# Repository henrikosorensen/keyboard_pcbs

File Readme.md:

GPLV2 licensed replacement keyboard PCBs.

# Omnikey 
Requires an Teensy++ 2.0 controller. - Firmware at https://github.com/qmk/qmk_firmware/tree/master/keyboards/omnikeyish

## Changelog

#### 1.3
* Nav cluster to Numpad cluster distance was off by 1/32 of an inch (0.7935mm). Meassurement confirmed on two original Omnikey PCBs and Plus rev3 plate. Not quite sure how I managed to assemble the first board.
* Rev1/3 Mounting holes got jumbled up in Schematic Reorganisation. Fixed now.

#### 1.1
* Teensy++ 2.0 uses pin D6 for an LED, so that interfers with the ROW5 assignment used on 1.0 boards. Moved ROW5 to pin E6

# AT101
Requires an Teensy 2.0 controller 

## Changelog

### 1.1
* Nav and numeric cluster distances to the alpha block were off by 1/32 inch.
* Big Arse Enter footprint updated, so stabiliser hole is large enough.

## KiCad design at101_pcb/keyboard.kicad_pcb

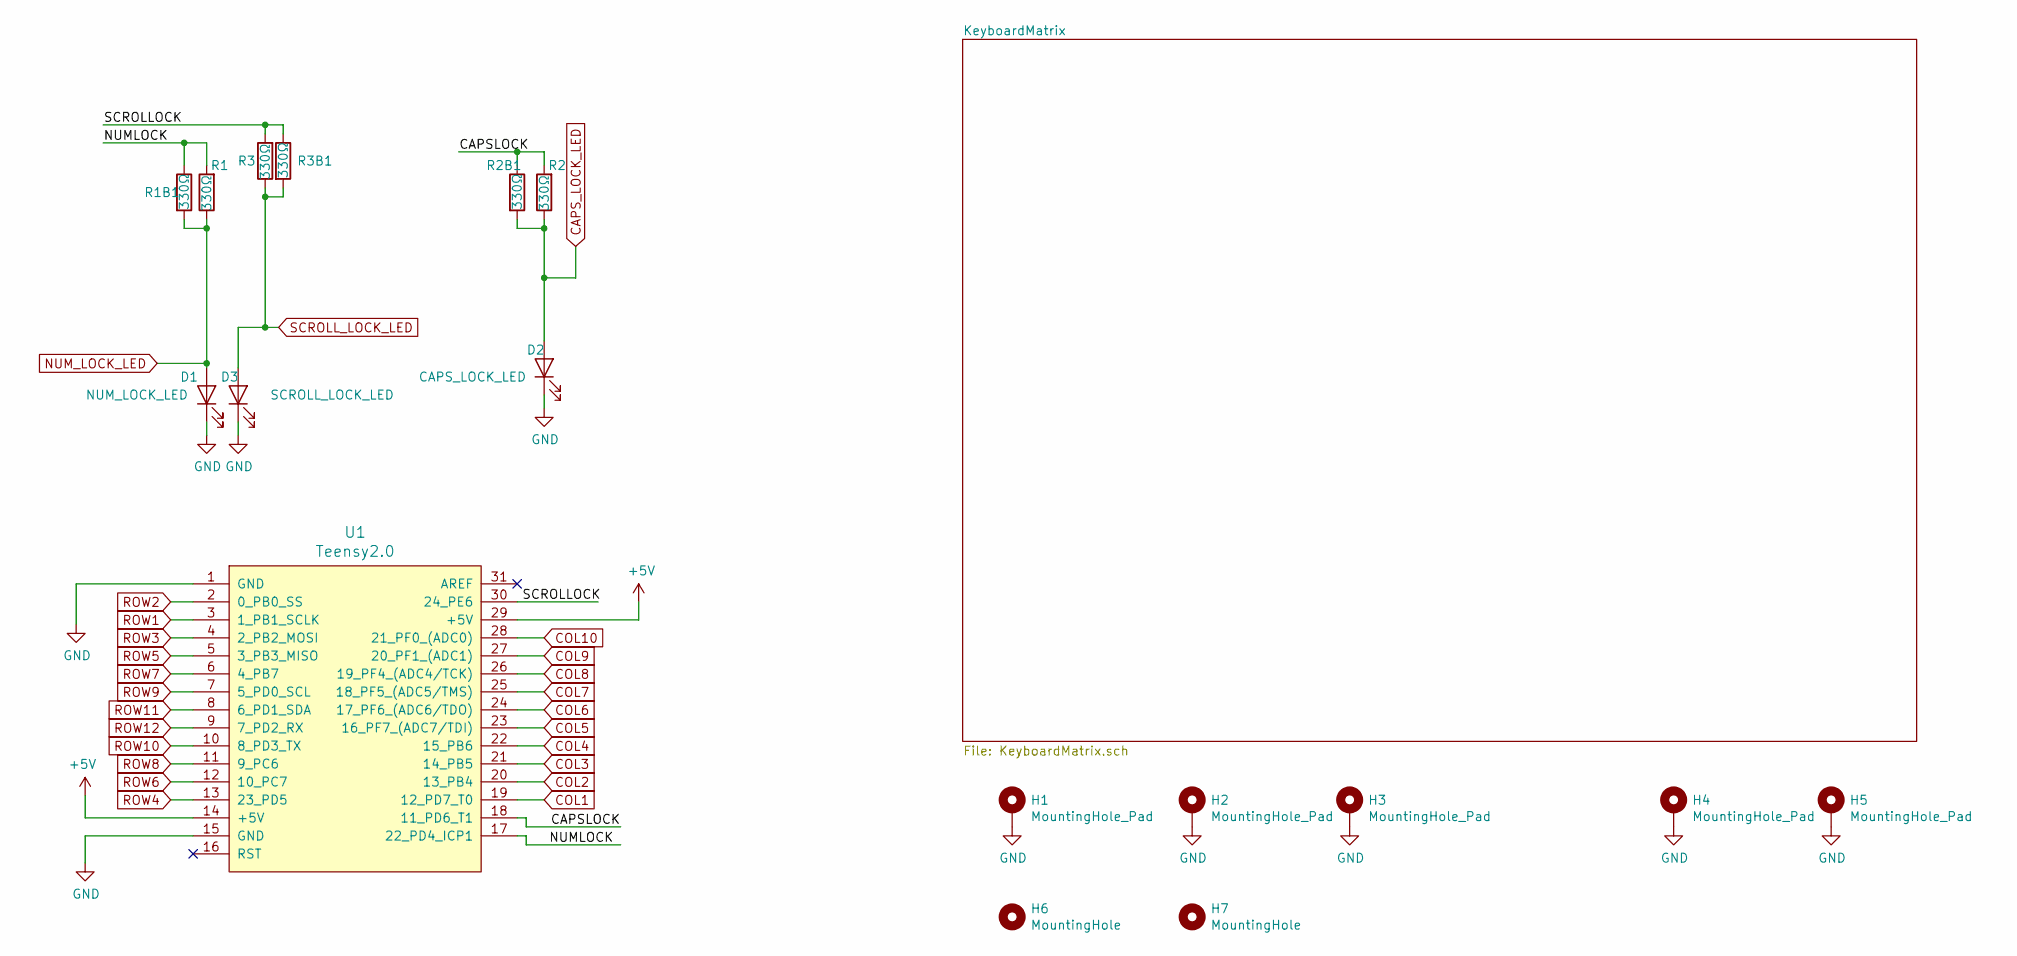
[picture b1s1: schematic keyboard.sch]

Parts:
D1: NUM_LOCK_LED; LED_Rectangular_W5.0mm_H2.0mm
D2: CAPS_LOCK_LED; LED_Rectangular_W5.0mm_H2.0mm
D3: SCROLL_LOCK_LED; LED_Rectangular_W5.0mm_H2.0mm
H1, H2, H3, H4, H5: MountingHole_Pad; MountingHole_3.7mm_Pad
H6, H7: MountingHole; MountingHole_11mm
R1, R2, R3: 330Ω; R_Axial_DIN0207_L6.3mm_D2.5mm_P10.16mm_Horizontal
R1B1, R2B1, R3B1: 330Ω; R_1206_3216Metric_Pad1.42x1.75mm_HandSolder
U1: Teensy2.0

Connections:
+5V: U1.14 (+5V), U1.29 (+5V)
/CAPSLOCK: R2.2, R2B1.1, U1.18 (11_PD6_T1)
/NUMLOCK: R1.2, R1B1.1, U1.17 (22_PD4_ICP1)
/SCROLLOCK: R3.2, R3B1.1, U1.30 (24_PE6)
CAPS_LOCK_LED: D2.2 (A), R2.1, R2B1.2
COL1: U1.19 (12_PD7_T0); also elsewhere on the board
COL2: U1.20 (13_PB4); also elsewhere on the board
COL3: U1.21 (14_PB5); also elsewhere on the board
COL4: U1.22 (15_PB6); also elsewhere on the board
COL5: U1.23 (16_PF7_(ADC7/TDI)); also elsewhere on the board
COL6: U1.24 (17_PF6_(ADC6/TDO)); also elsewhere on the board
COL7: U1.25 (18_PF5_(ADC5/TMS)); also elsewhere on the board
COL8: U1.26 (19_PF4_(ADC4/TCK)); also elsewhere on the board
COL9: U1.27 (20_PF1_(ADC1)); also elsewhere on the board
COL10: U1.28 (21_PF0_(ADC0)); also elsewhere on the board
GND: D1.1 (K), D2.1 (K), D3.1 (K), H1.1, H2.1, H3.1, H4.1, H5.1, U1.1 (GND), U1.15 (GND)
NUM_LOCK_LED: D1.2 (A), R1.1, R1B1.2
ROW1: U1.3 (1_PB1_SCLK); also elsewhere on the board
ROW2: U1.2 (0_PB0_SS); also elsewhere on the board
ROW3: U1.4 (2_PB2_MOSI); also elsewhere on the board
ROW4: U1.13 (23_PD5); also elsewhere on the board
ROW5: U1.5 (3_PB3_MISO); also elsewhere on the board
ROW6: U1.12 (10_PC7); also elsewhere on the board
ROW7: U1.6 (4_PB7); also elsewhere on the board
ROW8: U1.11 (9_PC6); also elsewhere on the board
ROW9: U1.7 (5_PD0_SCL); also elsewhere on the board
ROW10: U1.10 (8_PD3_TX); also elsewhere on the board
ROW11: U1.8 (6_PD1_SDA); also elsewhere on the board
ROW12: U1.9 (7_PD2_RX); also elsewhere on the board
SCROLL_LOCK_LED: D3.2 (A), R3.1, R3B1.2

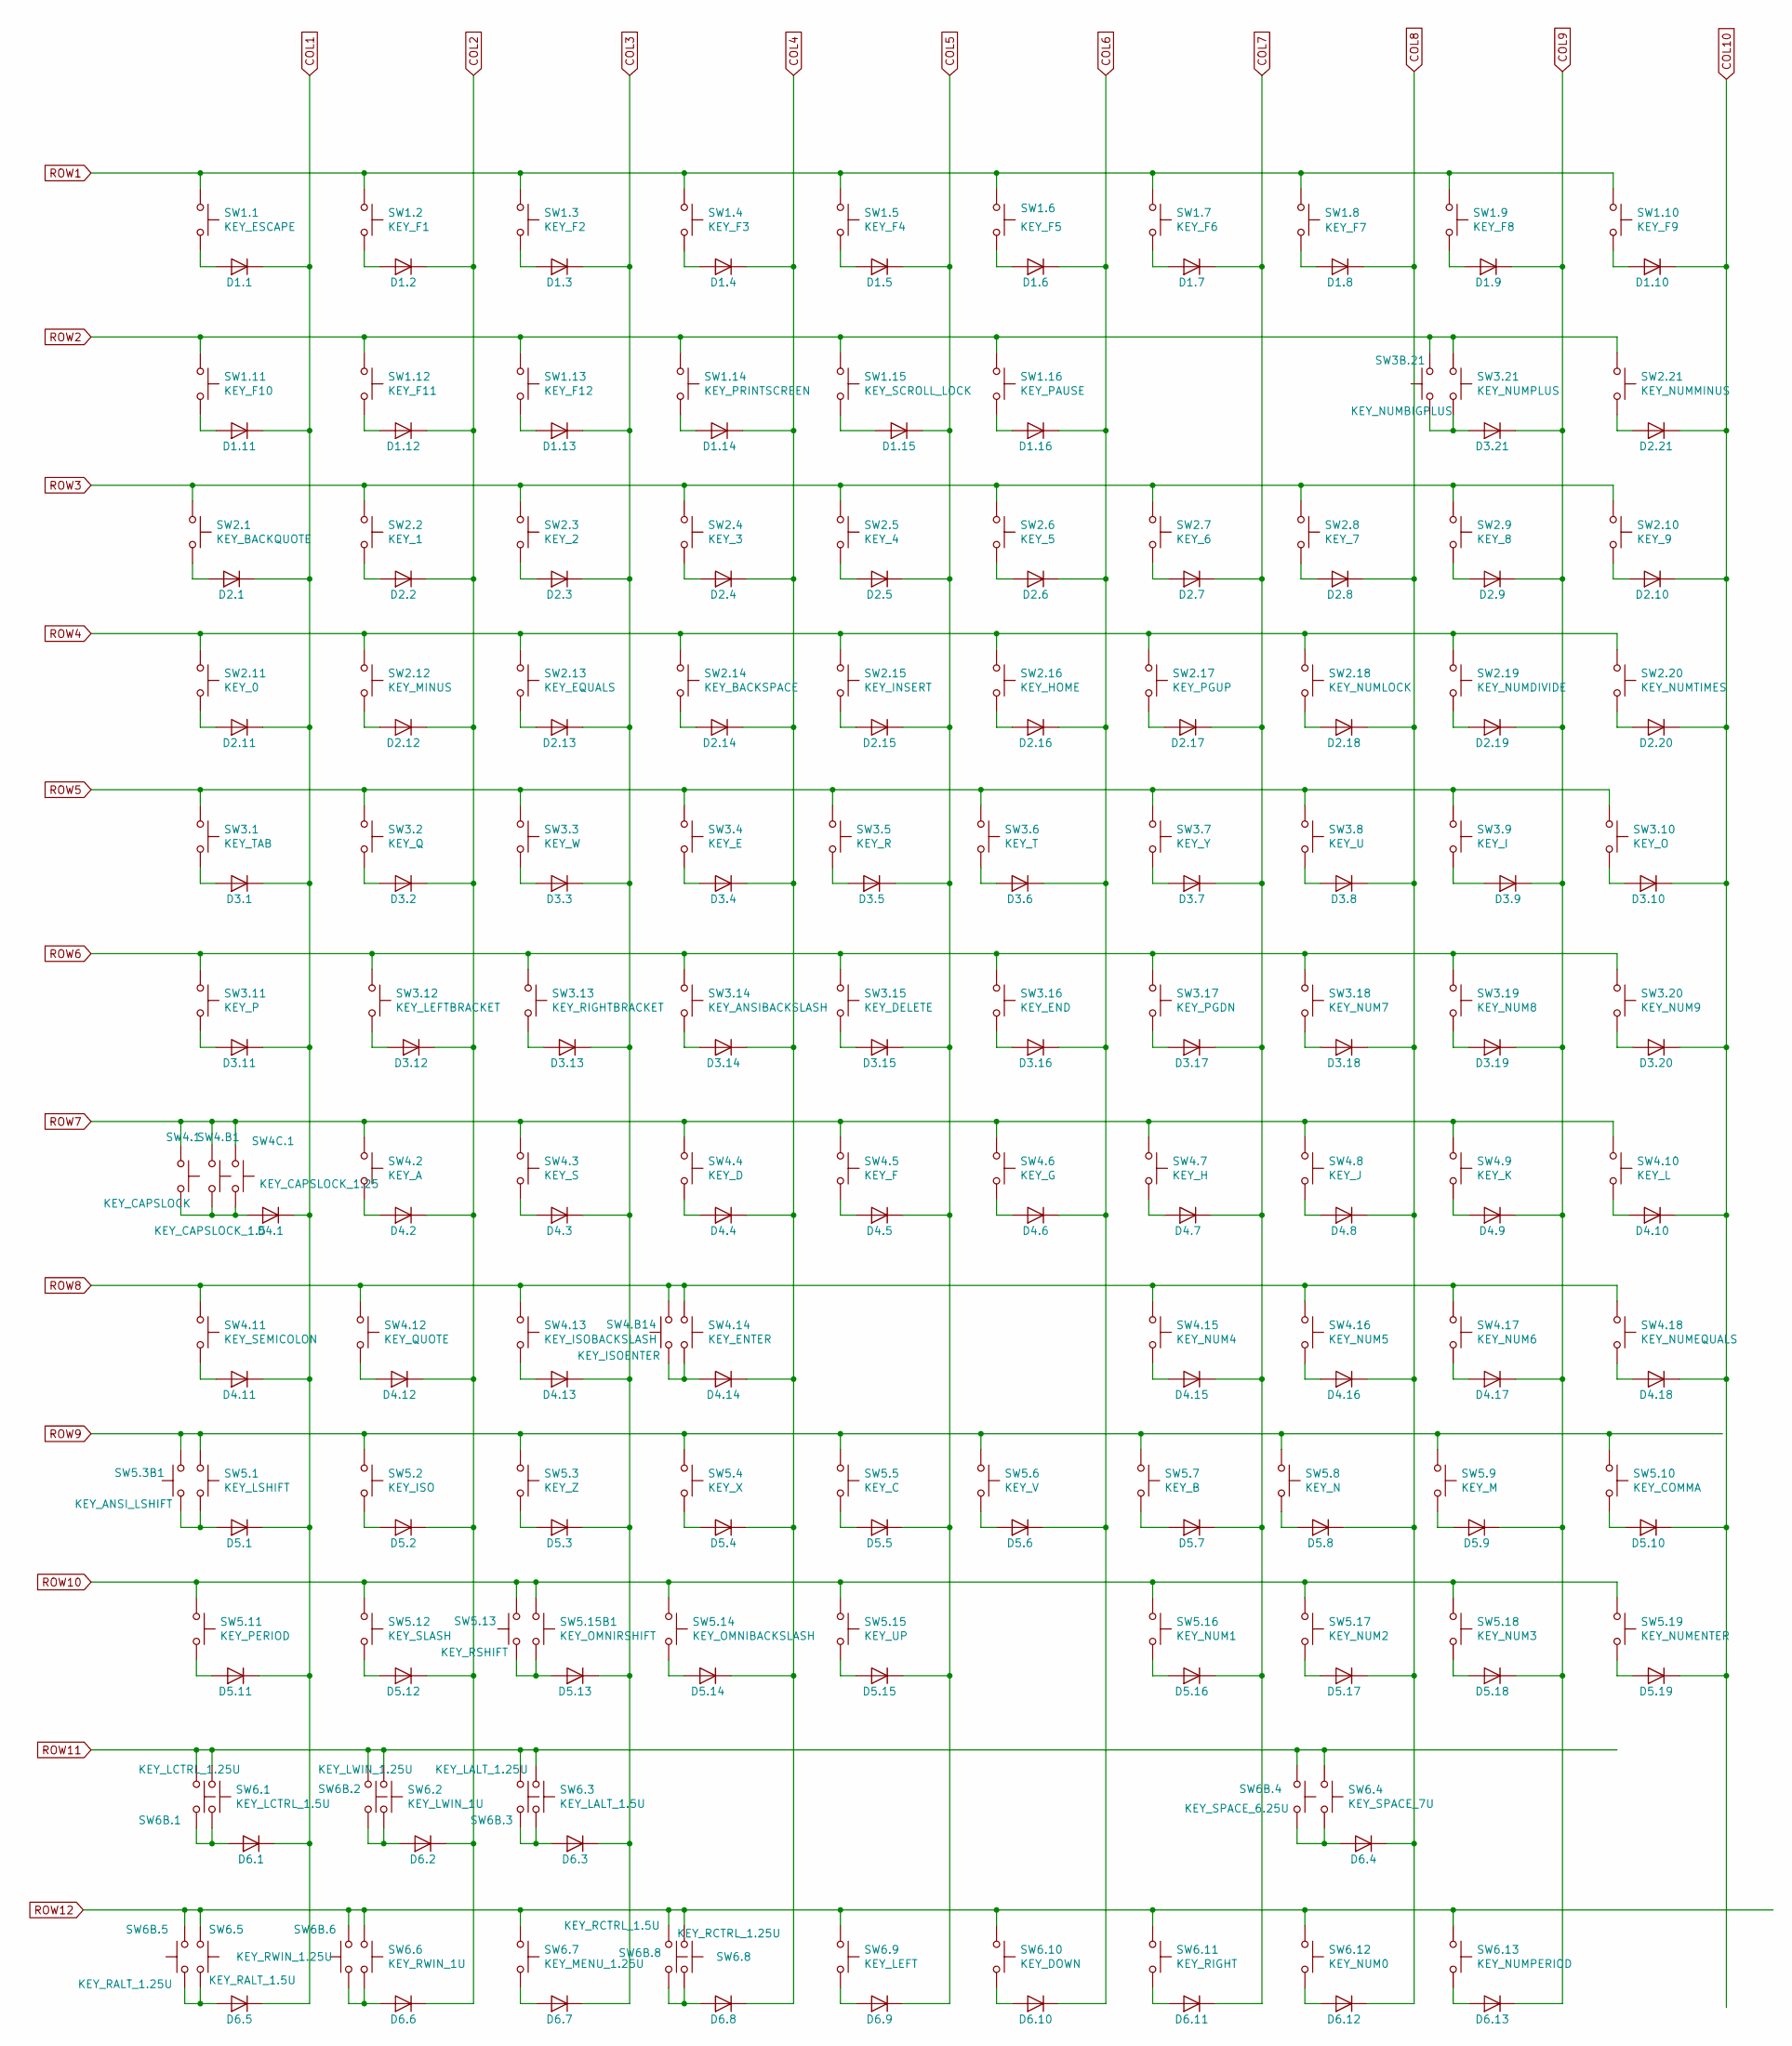
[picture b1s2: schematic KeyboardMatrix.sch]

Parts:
D1.1, D1.2, D1.3, D1.4, D1.5, D1.6, D1.7, D1.8, D1.9, D1.10, D1.11, D1.12, D1.13, D1.14, D1.15, D1.16, D2.1, D2.2, D2.3, D2.4, D2.5, D2.6, D2.7, D2.8, D2.9, D2.10, D2.11, D2.12, D2.13, D2.14, D2.15, D2.16, D2.17, D2.18, D2.19, D2.20, D2.21, D3.1, D3.2, D3.3, D3.4, D3.5, D3.6, D3.7, D3.8, D3.9, D3.10, D3.11, D3.12, D3.13, D3.14, D3.15, D3.16, D3.17, D3.18, D3.19, D3.20, D3.21, D4.1, D4.2, D4.3, D4.4, D4.5, D4.6, D4.7, D4.8, D4.9, D4.10, D4.11, D4.12, D4.13, D4.14, D4.15, D4.16, D4.17, D4.18, D5.1, D5.2, D5.3, D5.4, D5.5, D5.6, D5.7, D5.8, D5.9, D5.10, D5.11, D5.12, D5.13, D5.14, D5.15, D5.16, D5.17, D5.18, D5.19, D6.1, D6.2, D6.3, D6.4, D6.5, D6.6, D6.7, D6.8, D6.9, D6.10, D6.11, D6.12, D6.13: D; D_DO-35_SOD27_P7.62mm_Horizontal
SW1.1: KEY_ESCAPE; MX-1U-NoLED
SW1.2: KEY_F1; MX-1U-NoLED
SW1.3: KEY_F2; MX-1U-NoLED
SW1.4: KEY_F3; MX-1U-NoLED
SW1.5: KEY_F4; MX-1U-NoLED
SW1.6: KEY_F5; MX-1U-NoLED
SW1.7: KEY_F6; MX-1U-NoLED
SW1.8: KEY_F7; MX-1U-NoLED
SW1.9: KEY_F8; MX-1U-NoLED
SW1.10: KEY_F9; MX-1U-NoLED
SW1.11: KEY_F10; MX-1U-NoLED
SW1.12: KEY_F11; MX-1U-NoLED
SW1.13: KEY_F12; MX-1U-NoLED
SW1.14: KEY_PRINTSCREEN; MX-1U-NoLED
SW1.15: KEY_SCROLL_LOCK; MX-1U-NoLED
SW1.16: KEY_PAUSE; MX-1U-NoLED
SW2.1: KEY_BACKQUOTE; MX-1U-NoLED
SW2.2: KEY_1; MX-1U-NoLED
SW2.3: KEY_2; MX-1U-NoLED
SW2.4: KEY_3; MX-1U-NoLED
SW2.5: KEY_4; MX-1U-NoLED
SW2.6: KEY_5; MX-1U-NoLED
SW2.7: KEY_6; MX-1U-NoLED
SW2.8: KEY_7; MX-1U-NoLED
SW2.9: KEY_8; MX-1U-NoLED
SW2.10: KEY_9; MX-1U-NoLED
SW2.11: KEY_0; MX-1U-NoLED
SW2.12: KEY_MINUS; MX-1U-NoLED
SW2.13: KEY_EQUALS; MX-1U-NoLED
SW2.14: KEY_BACKSPACE; MX-2U-NoLED
SW2.15: KEY_INSERT; MX-1U-NoLED
SW2.16: KEY_HOME; MX-1U-NoLED
SW2.17: KEY_PGUP; MX-1U-NoLED
SW2.18: KEY_NUMLOCK; MX-1U-NoLED
SW2.19: KEY_NUMDIVIDE; MX-1U-NoLED
SW2.20: KEY_NUMTIMES; MX-1U-NoLED
SW2.21: KEY_NUMMINUS; MX-1U-NoLED
SW3.1: KEY_TAB; MX-1.5U-NoLED
SW3.2: KEY_Q; MX-1U-NoLED
SW3.3: KEY_W; MX-1U-NoLED
SW3.4: KEY_E; MX-1U-NoLED
SW3.5: KEY_R; MX-1U-NoLED
SW3.6: KEY_T; MX-1U-NoLED
SW3.7: KEY_Y; MX-1U-NoLED
SW3.8: KEY_U; MX-1U-NoLED
SW3.9: KEY_I; MX-1U-NoLED
SW3.10: KEY_O; MX-1U-NoLED
SW3.11: KEY_P; MX-1U-NoLED
SW3.12: KEY_LEFTBRACKET; MX-1U-NoLED
SW3.13: KEY_RIGHTBRACKET; MX-1U-NoLED
SW3.14: KEY_ANSIBACKSLASH; MX-1.5U-NoLED
SW3.15: KEY_DELETE; MX-1U-NoLED
SW3.16: KEY_END; MX-1U-NoLED
SW3.17: KEY_PGDN; MX-1U-NoLED
SW3.18: KEY_NUM7; MX-1U-NoLED
SW3.19: KEY_NUM8; MX-1U-NoLED
SW3.20: KEY_NUM9; MX-1U-NoLED
SW3.21: KEY_NUMPLUS; MX-1U-NoLED
SW3B.21: KEY_NUMBIGPLUS; MX-2U-NoLED
SW4.1: KEY_CAPSLOCK; MX-1.75U-NoLED
SW4.2: KEY_A; MX-1U-NoLED
SW4.3: KEY_S; MX-1U-NoLED
SW4.4: KEY_D; MX-1U-NoLED
SW4.5: KEY_F; MX-1U-NoLED
SW4.6: KEY_G; MX-1U-NoLED
SW4.7: KEY_H; MX-1U-NoLED
SW4.8: KEY_J; MX-1U-NoLED
SW4.9: KEY_K; MX-1U-NoLED
SW4.10: KEY_L; MX-1U-NoLED
SW4.11: KEY_SEMICOLON; MX-1U-NoLED
SW4.12: KEY_QUOTE; MX-1U-NoLED
SW4.13: KEY_ISOBACKSLASH; MX-1U-NoLED
SW4.14: KEY_ENTER; MX-Big-Ass-Enter-NoLED
SW4.15: KEY_NUM4; MX-1U-NoLED
SW4.16: KEY_NUM5; MX-1U-NoLED
SW4.17: KEY_NUM6; MX-1U-NoLED
SW4.18: KEY_NUMEQUALS; MX-1U-NoLED
SW4.B1: KEY_CAPSLOCK_1.5; MX-1.5U-NoLED
SW4.B14: KEY_ISOENTER; MX-ISO-ReversedStabilizers-NoLED
SW4C.1: KEY_CAPSLOCK_1.25; MX-1.25U-NoLED
SW5.1: KEY_LSHIFT; MX-1.25U-NoLED
SW5.2: KEY_ISO; MX-1U-NoLED
SW5.3: KEY_Z; MX-1U-NoLED
SW5.3B1: KEY_ANSI_LSHIFT; MX-2.25U-NoLED
SW5.4: KEY_X; MX-1U-NoLED
SW5.5: KEY_C; MX-1U-NoLED
SW5.6: KEY_V; MX-1U-NoLED
SW5.7: KEY_B; MX-1U-NoLED
SW5.8: KEY_N; MX-1U-NoLED
SW5.9: KEY_M; MX-1U-NoLED
SW5.10: KEY_COMMA; MX-1U-NoLED
SW5.11: KEY_PERIOD; MX-1U-NoLED
SW5.12: KEY_SLASH; MX-1U-NoLED
SW5.13: KEY_RSHIFT; MX-2.75U-NoLED
SW5.14: KEY_OMNIBACKSLASH; MX-1U-NoLED
SW5.15: KEY_UP; MX-1U-NoLED
SW5.15B1: KEY_OMNIRSHIFT; MX-1.75U-NoLED
SW5.16: KEY_NUM1; MX-1U-NoLED
SW5.17: KEY_NUM2; MX-1U-NoLED
SW5.18: KEY_NUM3; MX-1U-NoLED
SW5.19: KEY_NUMENTER; MX-2U-NoLED
SW6.1: KEY_LCTRL_1.5U; MX-1.5U-NoLED
SW6.2: KEY_LWIN_1U; MX-1U-NoLED
SW6.3: KEY_LALT_1.5U; MX-1.5U-NoLED
SW6.4: KEY_SPACE_7U; MX-7U-ReversedStabilizers-NoLED
SW6.5: KEY_RALT_1.5U; MX-1.5U-NoLED
SW6.6: KEY_RWIN_1U; MX-1U-NoLED
SW6.7: KEY_MENU_1.25U; MX-1.25U-NoLED
SW6.8: KEY_RCTRL_1.5U; MX-1.5U-NoLED
SW6.9: KEY_LEFT; MX-1U-NoLED
SW6.10: KEY_DOWN; MX-1U-NoLED
SW6.11: KEY_RIGHT; MX-1U-NoLED
SW6.12: KEY_NUM0; MX-2U-ReversedStabilizers-NoLED
SW6.13: KEY_NUMPERIOD; MX-1U-NoLED
SW6B.1: KEY_LCTRL_1.25U; MX-1.25U-NoLED
SW6B.2: KEY_LWIN_1.25U; MX-1.25U-NoLED
SW6B.3: KEY_LALT_1.25U; MX-1.25U-NoLED
SW6B.4: KEY_SPACE_6.25U; MX-6.25U-ReversedStabilizers-NoLED
SW6B.5: KEY_RALT_1.25U; MX-1.25U-NoLED
SW6B.6: KEY_RWIN_1.25U; MX-1.25U-NoLED
SW6B.8: KEY_RCTRL_1.25U; MX-1.25U-NoLED

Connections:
COL1: D1.1.1 (K), D1.11.1 (K), D2.1.1 (K), D2.11.1 (K), D3.1.1 (K), D3.11.1 (K), D4.1.1 (K), D4.11.1 (K), D5.1.1 (K), D5.11.1 (K), D6.1.1 (K), D6.5.1 (K); also elsewhere on the board
COL2: D1.2.1 (K), D1.12.1 (K), D2.2.1 (K), D2.12.1 (K), D3.2.1 (K), D3.12.1 (K), D4.2.1 (K), D4.12.1 (K), D5.2.1 (K), D5.12.1 (K), D6.2.1 (K), D6.6.1 (K); also elsewhere on the board
COL3: D1.3.1 (K), D1.13.1 (K), D2.3.1 (K), D2.13.1 (K), D3.3.1 (K), D3.13.1 (K), D4.3.1 (K), D4.13.1 (K), D5.3.1 (K), D5.13.1 (K), D6.3.1 (K), D6.7.1 (K); also elsewhere on the board
COL4: D1.4.1 (K), D1.14.1 (K), D2.4.1 (K), D2.14.1 (K), D3.4.1 (K), D3.14.1 (K), D4.4.1 (K), D4.14.1 (K), D5.4.1 (K), D5.14.1 (K), D6.8.1 (K); also elsewhere on the board
COL5: D1.5.1 (K), D1.15.1 (K), D2.5.1 (K), D2.15.1 (K), D3.5.1 (K), D3.15.1 (K), D4.5.1 (K), D5.5.1 (K), D5.15.1 (K), D6.9.1 (K); also elsewhere on the board
COL6: D1.6.1 (K), D1.16.1 (K), D2.6.1 (K), D2.16.1 (K), D3.6.1 (K), D3.16.1 (K), D4.6.1 (K), D5.6.1 (K), D6.10.1 (K); also elsewhere on the board
COL7: D1.7.1 (K), D2.7.1 (K), D2.17.1 (K), D3.7.1 (K), D3.17.1 (K), D4.7.1 (K), D4.15.1 (K), D5.7.1 (K), D5.16.1 (K), D6.11.1 (K); also elsewhere on the board
COL8: D1.8.1 (K), D2.8.1 (K), D2.18.1 (K), D3.8.1 (K), D3.18.1 (K), D4.8.1 (K), D4.16.1 (K), D5.8.1 (K), D5.17.1 (K), D6.4.1 (K), D6.12.1 (K); also elsewhere on the board
COL9: D1.9.1 (K), D2.9.1 (K), D2.19.1 (K), D3.9.1 (K), D3.19.1 (K), D3.21.1 (K), D4.9.1 (K), D4.17.1 (K), D5.9.1 (K), D5.18.1 (K), D6.13.1 (K); also elsewhere on the board
COL10: D1.10.1 (K), D2.10.1 (K), D2.20.1 (K), D2.21.1 (K), D3.10.1 (K), D3.20.1 (K), D4.10.1 (K), D4.18.1 (K), D5.10.1 (K), D5.19.1 (K); also elsewhere on the board
unnamed: D1.1.2 (A), SW1.1.2
unnamed: D1.2.2 (A), SW1.2.2
unnamed: D1.3.2 (A), SW1.3.2
unnamed: D1.4.2 (A), SW1.4.2
unnamed: D1.5.2 (A), SW1.5.2
unnamed: D1.6.2 (A), SW1.6.2
unnamed: D1.7.2 (A), SW1.7.2
unnamed: D1.8.2 (A), SW1.8.2
unnamed: D1.9.2 (A), SW1.9.2
unnamed: D1.10.2 (A), SW1.10.2
unnamed: D1.11.2 (A), SW1.11.2
unnamed: D1.12.2 (A), SW1.12.2
unnamed: D1.13.2 (A), SW1.13.2
unnamed: D1.14.2 (A), SW1.14.2
unnamed: D1.15.2 (A), SW1.15.2
unnamed: D1.16.2 (A), SW1.16.2
unnamed: D2.1.2 (A), SW2.1.2
unnamed: D2.2.2 (A), SW2.2.2
unnamed: D2.3.2 (A), SW2.3.2
unnamed: D2.4.2 (A), SW2.4.2
unnamed: D2.5.2 (A), SW2.5.2
unnamed: D2.6.2 (A), SW2.6.2
unnamed: D2.7.2 (A), SW2.7.2
unnamed: D2.8.2 (A), SW2.8.2
unnamed: D2.9.2 (A), SW2.9.2
unnamed: D2.10.2 (A), SW2.10.2
unnamed: D2.11.2 (A), SW2.11.2
unnamed: D2.12.2 (A), SW2.12.2
unnamed: D2.13.2 (A), SW2.13.2
unnamed: D2.14.2 (A), SW2.14.2
unnamed: D2.15.2 (A), SW2.15.2
unnamed: D2.16.2 (A), SW2.16.2
unnamed: D2.17.2 (A), SW2.17.2
unnamed: D2.18.2 (A), SW2.18.2
unnamed: D2.19.2 (A), SW2.19.2
unnamed: D2.20.2 (A), SW2.20.2
unnamed: D2.21.2 (A), SW2.21.2
unnamed: D3.1.2 (A), SW3.1.2
unnamed: D3.2.2 (A), SW3.2.2
unnamed: D3.3.2 (A), SW3.3.2
unnamed: D3.4.2 (A), SW3.4.2
unnamed: D3.5.2 (A), SW3.5.2
unnamed: D3.6.2 (A), SW3.6.2
unnamed: D3.7.2 (A), SW3.7.2
unnamed: D3.8.2 (A), SW3.8.2
unnamed: D3.9.2 (A), SW3.9.2
unnamed: D3.10.2 (A), SW3.10.2
unnamed: D3.11.2 (A), SW3.11.2
unnamed: D3.12.2 (A), SW3.12.2
unnamed: D3.13.2 (A), SW3.13.2
unnamed: D3.14.2 (A), SW3.14.2
unnamed: D3.15.2 (A), SW3.15.2
unnamed: D3.16.2 (A), SW3.16.2
unnamed: D3.17.2 (A), SW3.17.2
unnamed: D3.18.2 (A), SW3.18.2
unnamed: D3.19.2 (A), SW3.19.2
unnamed: D3.20.2 (A), SW3.20.2
unnamed: D3.21.2 (A), SW3.21.2, SW3B.21.1
unnamed: D4.1.2 (A), SW4.1.2, SW4.B1.2, SW4C.1.2
unnamed: D4.2.2 (A), SW4.2.2
unnamed: D4.3.2 (A), SW4.3.2
unnamed: D4.4.2 (A), SW4.4.2
unnamed: D4.5.2 (A), SW4.5.2
unnamed: D4.6.2 (A), SW4.6.2
unnamed: D4.7.2 (A), SW4.7.2
unnamed: D4.8.2 (A), SW4.8.2
unnamed: D4.9.2 (A), SW4.9.2
unnamed: D4.10.2 (A), SW4.10.2
unnamed: D4.11.2 (A), SW4.11.2
unnamed: D4.12.2 (A), SW4.12.2
unnamed: D4.13.2 (A), SW4.13.2
unnamed: D4.14.2 (A), SW4.14.2, SW4.B14.1
unnamed: D4.15.2 (A), SW4.15.2
unnamed: D4.16.2 (A), SW4.16.2
unnamed: D4.17.2 (A), SW4.17.2
unnamed: D4.18.2 (A), SW4.18.2
unnamed: D5.1.2 (A), SW5.1.2, SW5.3B1.1
unnamed: D5.2.2 (A), SW5.2.2
unnamed: D5.3.2 (A), SW5.3.2
unnamed: D5.4.2 (A), SW5.4.2
unnamed: D5.5.2 (A), SW5.5.2
unnamed: D5.6.2 (A), SW5.6.2
unnamed: D5.7.2 (A), SW5.7.2
unnamed: D5.8.2 (A), SW5.8.2
unnamed: D5.9.2 (A), SW5.9.2
unnamed: D5.10.2 (A), SW5.10.2
unnamed: D5.11.2 (A), SW5.11.2
unnamed: D5.12.2 (A), SW5.12.2
unnamed: D5.13.2 (A), SW5.13.1, SW5.15B1.2
unnamed: D5.14.2 (A), SW5.14.2
unnamed: D5.15.2 (A), SW5.15.2
unnamed: D5.16.2 (A), SW5.16.2
unnamed: D5.17.2 (A), SW5.17.2
unnamed: D5.18.2 (A), SW5.18.2
unnamed: D5.19.2 (A), SW5.19.2
unnamed: D6.1.2 (A), SW6.1.2, SW6B.1.2
unnamed: D6.2.2 (A), SW6.2.2, SW6B.2.2
unnamed: D6.3.2 (A), SW6.3.2, SW6B.3.2
unnamed: D6.4.2 (A), SW6.4.2, SW6B.4.2
unnamed: D6.5.2 (A), SW6.5.2, SW6B.5.1
unnamed: D6.6.2 (A), SW6.6.2, SW6B.6.1
unnamed: D6.7.2 (A), SW6.7.2
unnamed: D6.8.2 (A), SW6.8.2, SW6B.8.2
unnamed: D6.9.2 (A), SW6.9.2
unnamed: D6.10.2 (A), SW6.10.2
unnamed: D6.11.2 (A), SW6.11.2
unnamed: D6.12.2 (A), SW6.12.2
unnamed: D6.13.2 (A), SW6.13.2
ROW1: SW1.1.1, SW1.2.1, SW1.3.1, SW1.4.1, SW1.5.1, SW1.6.1, SW1.7.1, SW1.8.1, SW1.9.1, SW1.10.1; also elsewhere on the board
ROW2: SW1.11.1, SW1.12.1, SW1.13.1, SW1.14.1, SW1.15.1, SW1.16.1, SW2.21.1, SW3.21.1, SW3B.21.2; also elsewhere on the board
ROW3: SW2.1.1, SW2.2.1, SW2.3.1, SW2.4.1, SW2.5.1, SW2.6.1, SW2.7.1, SW2.8.1, SW2.9.1, SW2.10.1; also elsewhere on the board
ROW4: SW2.11.1, SW2.12.1, SW2.13.1, SW2.14.1, SW2.15.1, SW2.16.1, SW2.17.1, SW2.18.1, SW2.19.1, SW2.20.1; also elsewhere on the board
ROW5: SW3.1.1, SW3.2.1, SW3.3.1, SW3.4.1, SW3.5.1, SW3.6.1, SW3.7.1, SW3.8.1, SW3.9.1, SW3.10.1; also elsewhere on the board
ROW6: SW3.11.1, SW3.12.1, SW3.13.1, SW3.14.1, SW3.15.1, SW3.16.1, SW3.17.1, SW3.18.1, SW3.19.1, SW3.20.1; also elsewhere on the board
ROW7: SW4.1.1, SW4.2.1, SW4.3.1, SW4.4.1, SW4.5.1, SW4.6.1, SW4.7.1, SW4.8.1, SW4.9.1, SW4.10.1, SW4.B1.1, SW4C.1.1; also elsewhere on the board
ROW8: SW4.11.1, SW4.12.1, SW4.13.1, SW4.14.1, SW4.15.1, SW4.16.1, SW4.17.1, SW4.18.1, SW4.B14.2; also elsewhere on the board
ROW9: SW5.1.1, SW5.2.1, SW5.3.1, SW5.3B1.2, SW5.4.1, SW5.5.1, SW5.6.1, SW5.7.1, SW5.8.1, SW5.9.1, SW5.10.1; also elsewhere on the board
ROW10: SW5.11.1, SW5.12.1, SW5.13.2, SW5.14.1, SW5.15.1, SW5.15B1.1, SW5.16.1, SW5.17.1, SW5.18.1, SW5.19.1; also elsewhere on the board
ROW11: SW6.1.1, SW6.2.1, SW6.3.1, SW6.4.1, SW6B.1.1, SW6B.2.1, SW6B.3.1, SW6B.4.1; also elsewhere on the board
ROW12: SW6.5.1, SW6.6.1, SW6.7.1, SW6.8.1, SW6.9.1, SW6.10.1, SW6.11.1, SW6.12.1, SW6.13.1, SW6B.5.2, SW6B.6.2, SW6B.8.1; also elsewhere on the board

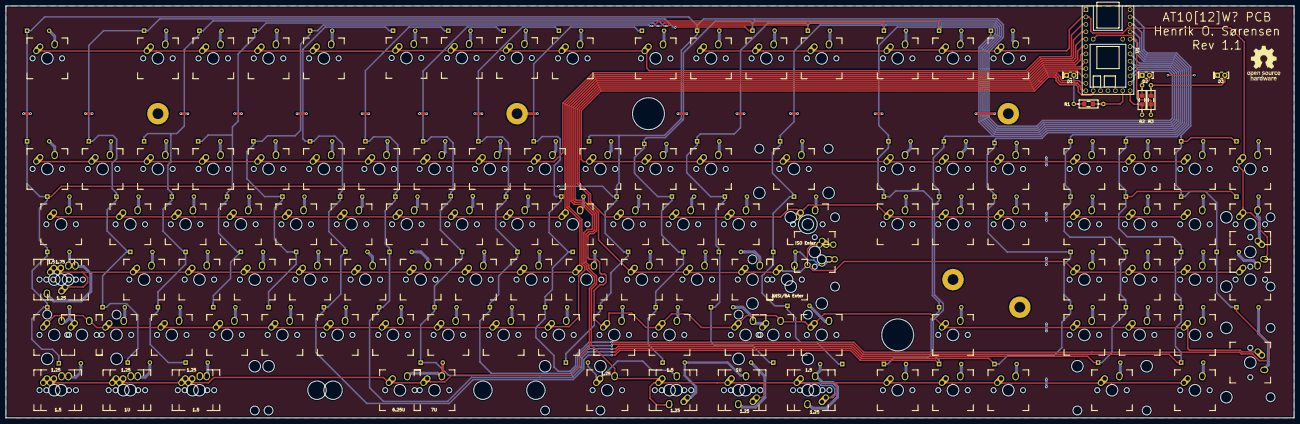
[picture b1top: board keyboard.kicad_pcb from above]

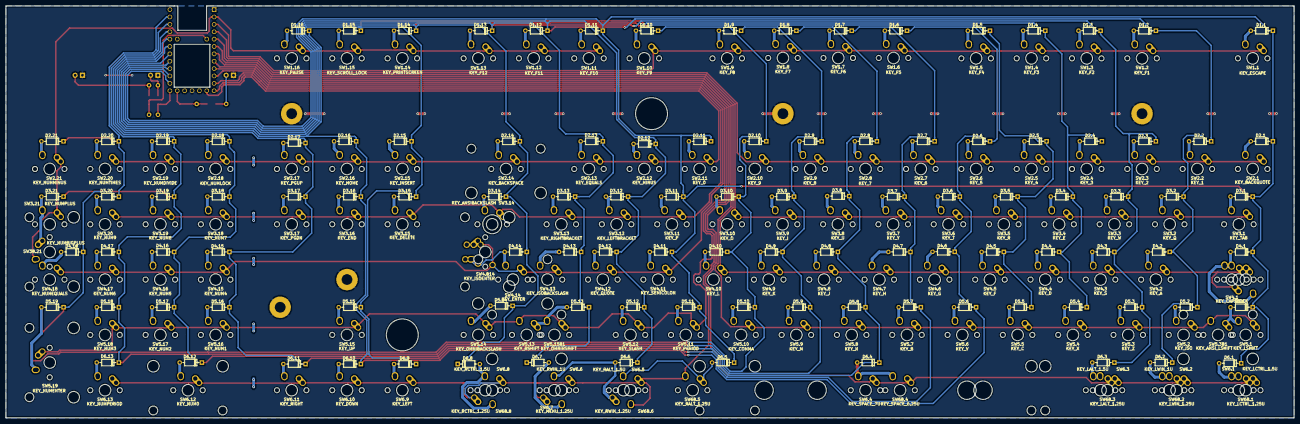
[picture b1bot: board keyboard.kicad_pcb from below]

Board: 2 copper layers, 443.7 x 141.9 mm, 246 parts (108 on the bottom side), 138 nets.

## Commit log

2019-06-15 Omnikeyish kicad files
2019-06-15 Add Dell AT10[12]W? PCB kicad file
2019-06-15 Add license file
2019-06-15 Add generated kicad files to .gitignore
2019-06-20 Rev 1.2: Fix brainfart matrix postion for Ultra's 1.5u insert and delete keys was wrong
2019-06-21 Tweak silk screen location of 2u numpad plus
2019-06-23 Nav cluster to Numpad cluster distance was off by 1/32 of an inch (0.7935mm).
2019-07-06 Correct AT10[12]W? switch labels
2019-07-06 Correct nav and numeric cluster distances
2019-07-07 Update Big Arse Enter footprint.
2019-07-23 Add schematic and gerber output for ease of use by github vistors
